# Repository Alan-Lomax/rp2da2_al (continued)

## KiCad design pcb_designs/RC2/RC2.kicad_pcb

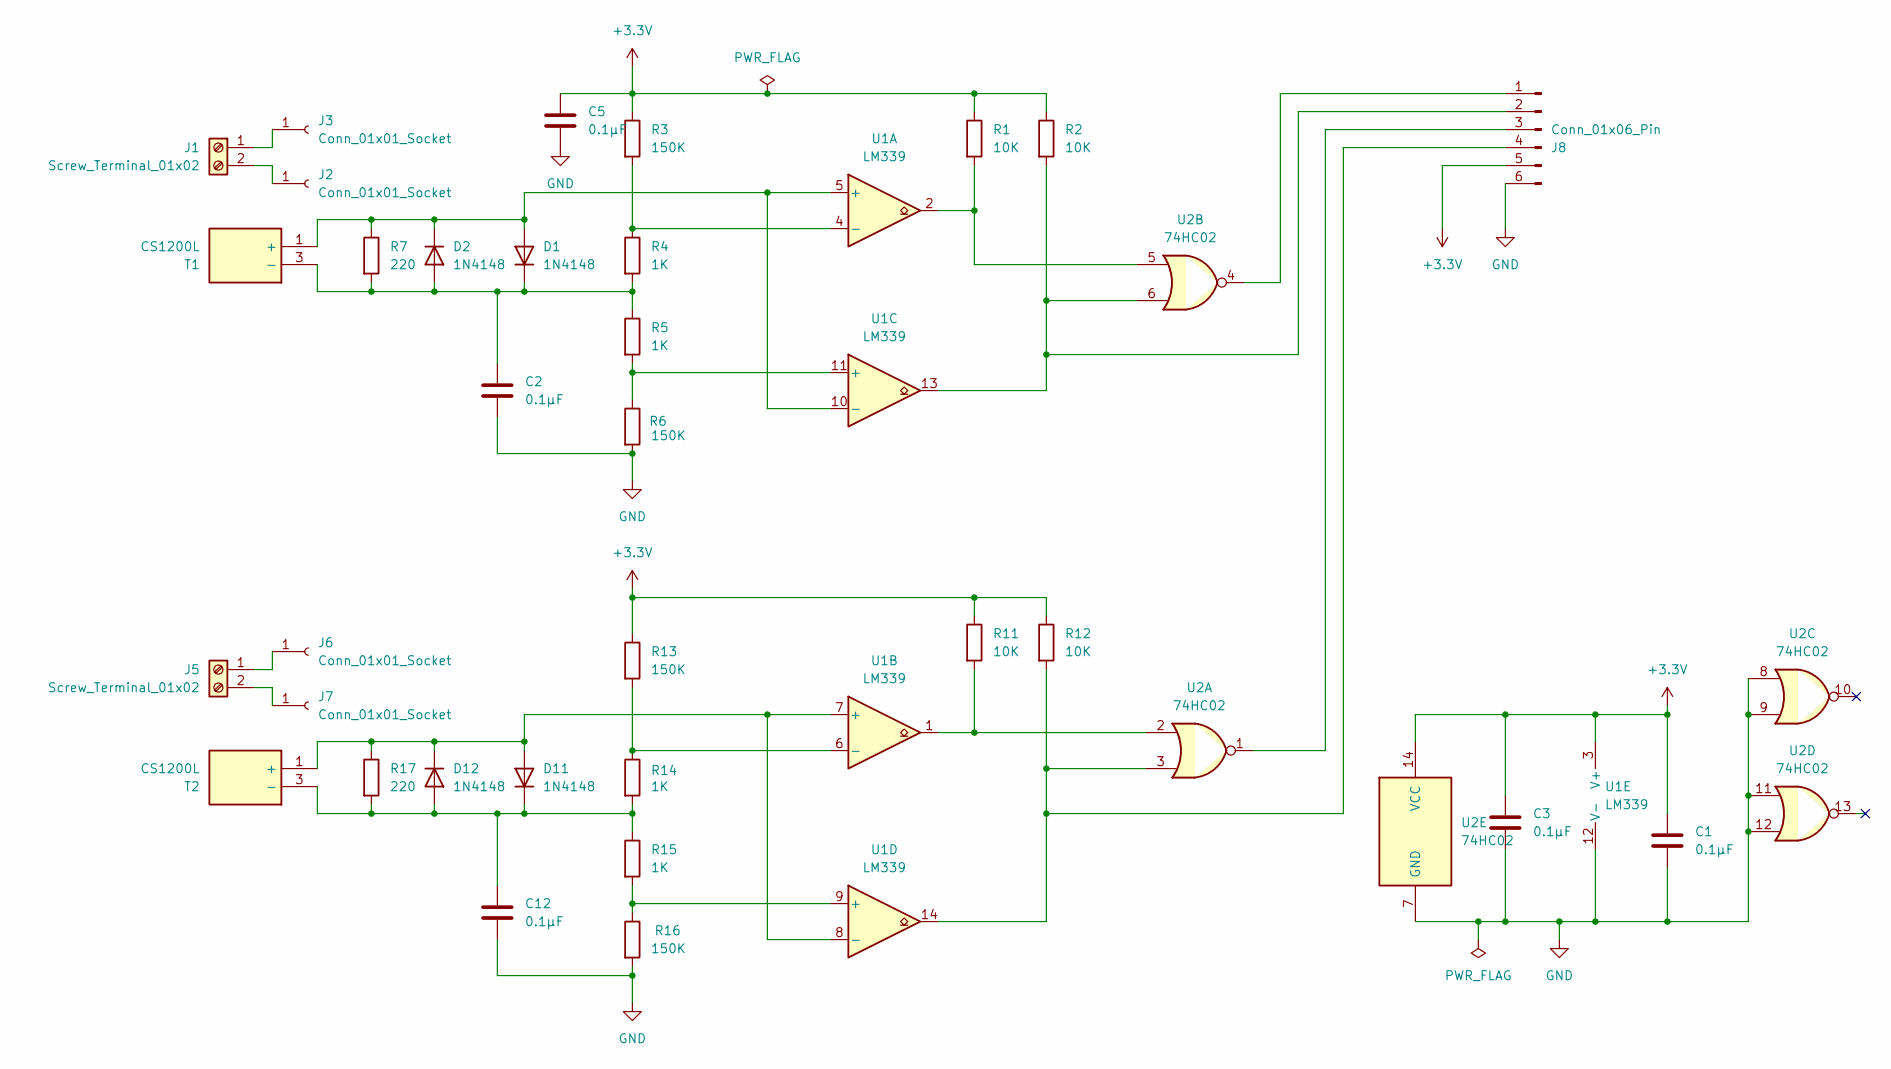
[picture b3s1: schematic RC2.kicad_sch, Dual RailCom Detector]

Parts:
C1, C2, C3, C5, C12: 0.1µF; C_Disc_D7.0mm_W2.5mm_P5.00mm
D1, D2, D11, D12: 1N4148; D_DO-35_SOD27_P7.62mm_Horizontal
J1, J5: Screw_Terminal_01x02; TerminalBlock_bornier-2_P5.08mm
J2, J3, J6, J7: Conn_01x01_Socket; SolderWire-0.5sqmm_1x01_D0.9mm_OD2.1mm
J8: Conn_01x06_Pin; Molex_KK-254_AE-6410-06A_1x06_P2.54mm_Vertical
R1, R2, R11, R12: 10K; R_Axial_DIN0207_L6.3mm_D2.5mm_P7.62mm_Horizontal
R3, R6, R13, R16: 150K; R_Axial_DIN0207_L6.3mm_D2.5mm_P7.62mm_Horizontal
R4, R5, R14, R15: 1K; R_Axial_DIN0207_L6.3mm_D2.5mm_P7.62mm_Horizontal
R7, R17: 220; R_Axial_DIN0207_L6.3mm_D2.5mm_P7.62mm_Horizontal
T1, T2: CS1200L; Manufacturer_Part_Number CS1200L; Mouser Part Number 994-CS1200L
U1: LM339; DIP-14_W7.62mm
U2: 74HC02; DIP-14_W7.62mm

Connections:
+3.3V: C1.1, C3.1, C5.1, J8.5, R1.1, R2.1, R3.1, R11.1, R12.1, R13.1, U1.3 (V+), U2.14 (VCC)
GND: C1.2, C2.2, C3.2, C5.2, C12.2, J8.6, R6.2, R16.2, U1.12 (V-), U2.7 (GND), U2.8, U2.9, U2.11, U2.12
unnamed: D1.2 (A), D2.1 (K), R7.1, T1.1 (+), U1.5 (+), U1.10 (-)
unnamed: C2.1, D1.1 (K), D2.2 (A), R4.2, R5.1, R7.2, T1.3 (-)
unnamed: D11.2 (A), D12.1 (K), R17.1, T2.1 (+), U1.7 (+), U1.8 (-)
unnamed: C12.1, D11.1 (K), D12.2 (A), R14.2, R15.1, R17.2, T2.3 (-)
unnamed: J1.1, J3.1
unnamed: J1.2, J2.1
unnamed: J5.1, J6.1
unnamed: J5.2, J7.1
unnamed: J8.1, U2.4
unnamed: J8.2, R2.2, U1.13, U2.6
unnamed: J8.3, U2.1
unnamed: J8.4, R12.2, U1.14, U2.3
unnamed: R1.2, U1.2, U2.5
unnamed: R11.2, U1.1, U2.2
unnamed: R3.2, R4.1, U1.4 (-)
unnamed: R13.2, R14.1, U1.6 (-)
unnamed: R5.2, R6.1, U1.11 (+)
unnamed: R15.2, R16.1, U1.9 (+)

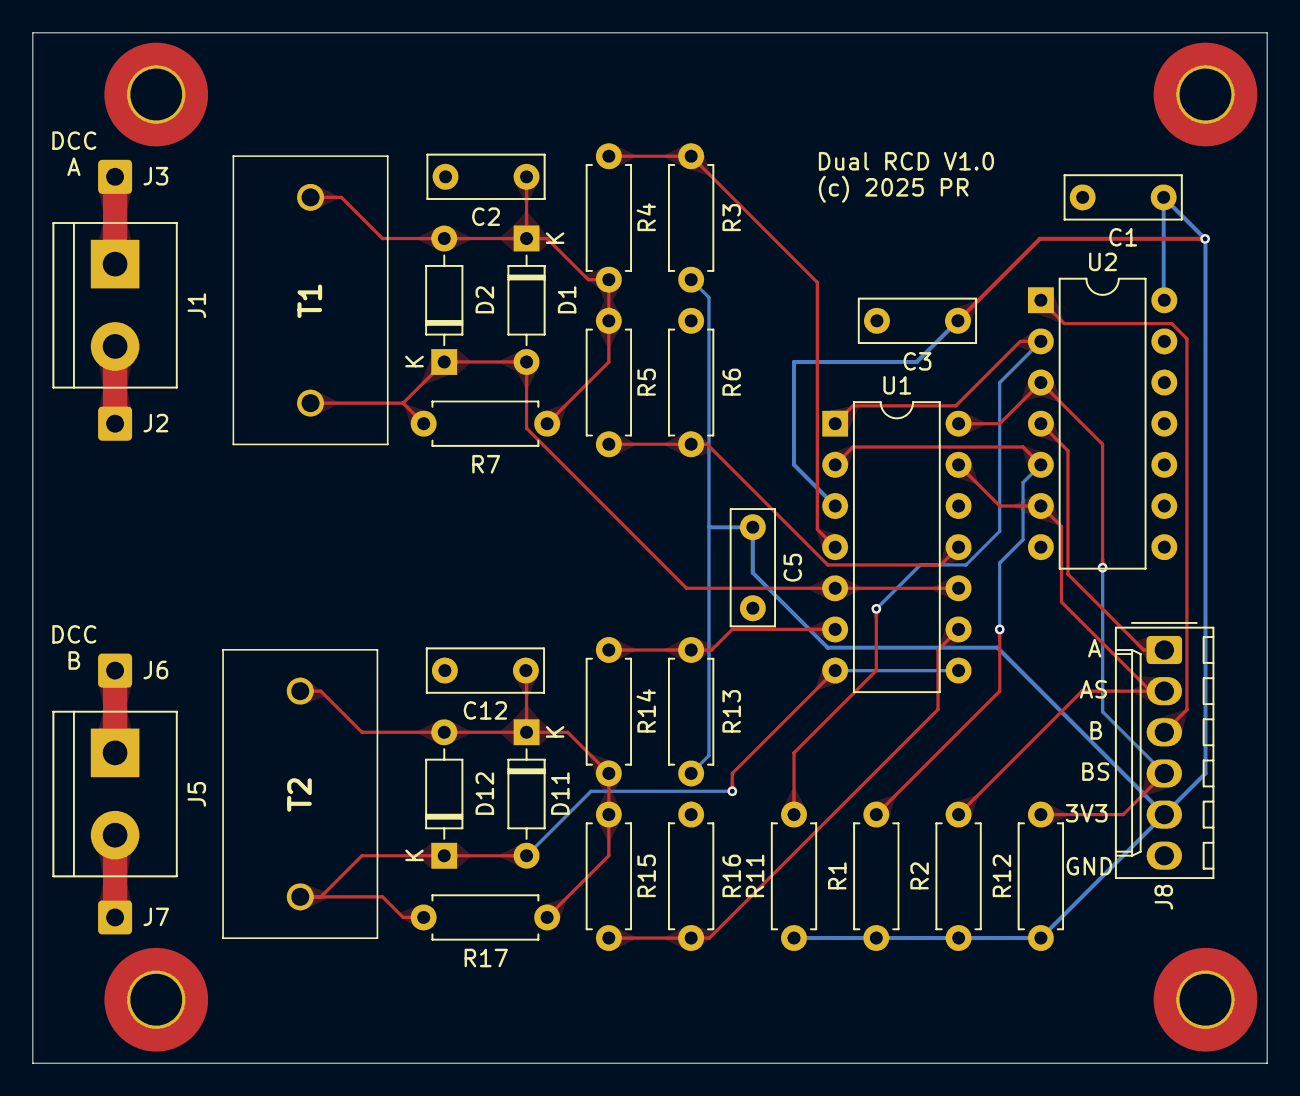
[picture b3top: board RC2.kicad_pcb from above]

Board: 2 copper layers, 76.2 x 63.6 mm, 34 parts (0 on the bottom side), 20 nets.

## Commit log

2025-04-23 Added diagnostics and other changes.
    This update provides additional diagnostic information on RailCom performance. There's also a bug fix related to parsing Channel 2 responses and other minor mostly cosmetic changes.
2025-04-29 PCB Design Added
    This update adds the Kicad PBC design to the repository.
    Software changes include improved start bit recognition and addition of the Programming on Main write CV function.
2025-05-26 Updated Schematic
    Up date to the dual detector schematic. N.B PCB layout to follow.
    Plus a few cosmetic code changes.
2025-06-03 New PCB Layout R2.1
    This new PCB Layout includes Raspberry Pi PICO footprint c/w Power Supply (12 VDC in to 5VDC out), A NeoPixel, an H Bridge Driver, an I2C OLED header, and many GPIO headers.
2025-06-03 GPIO Mappings etc.
    1. GPIO mappings for Pico changed to match PCB.
    2. GPIO allocations for DRV8874 _FAULT & Current Sense Added.
    3. README updated with installation instructions.
    4. Minor typos & bugs corrected.
2025-06-25 Orientation bit timing fix
    Fixes bug in reading orientation bit timing in PIO rx routine.
    git ignore Kicad lock files.
    Other cosmetic changes.
2025-06-25 kicad lock file removed
2025-07-16 Added PCB RC3
    Added Integrated Command Station PCB Design.
    Cosmetic changes to software.
2025-09-03 Tighten RailCom window timings etc
    Review and tighten RailCom window timings.
    Improved diagnostics and statistics.
    Refactoring to streamline timer callbacks.
    Cosmetic changes to formatting.
2025-09-11 RailCom Channel 1 improvements
    Elimination of potential race conditions on RailCom Channel 1.
    Plus the usual minor cosmetic stuff.
2025-10-03 asyncio introduction
    Refactor and modify MQTT interface to use asyncio.
2025-10-03 Als quality review. Very minor readability issues.
    Duplicated the GNDPWR symbol and used it to eliminated many crossed lines.
2025-10-08 Added RC3_PCB_R1b folder and contents
2025-10-09 Quad local detector
    Add example main.py for quad local detector.
    Minor bugs.
    Refactoring to improve RailCom decode performance.
2025-10-09 PCB Designs Split to new repo
    PCB Designs are now in rp2da2-pcb
2025-11-03 Update test_dccrc1.py
    Fix reference to undeclared pin
2026-03-25 Updates for board RC_LCL_4 Rev 0.B
    Updates to allow Revision 0.B of the RC_LCL-4 board.
    Other minor and cosmetic changes.
2026-05-07 Refactor local detectors, ADC, PIO and docs
    Large refactor and docs updates to improve local detector reliability and usability. Key changes: add dcc_pin support to local RCom detectors and pass DCC sense pin from examples; rewrite ADC reading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
2026-05-30 Publish RailCom ch2 dynamic info; UI/README fixes
    Add end-to-end support for RailCom Channel-2 dynamic information and several UI/docs fixes.
    Key changes:
    - RComCmdRsp (rp2dcc/dcc_rc_ch2.py): make detector a singleton, store dynamic values, enqueue changed addresses with a bounded deque, and signal queue-full via Device.CH2_Q_FULL. Provide get_instance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
    - MQTT publishing (lib/mqtt_cmd.py): start a background _pub_check task in Cab to poll RComCmdRsp.get_dyn_chng() and publish JSON payloads to rcom/gbl/{addr}/id7. Add _DYN_INFO_ENCODE mapping and rep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
    - Screen/UI (lib/screen.py): handle and display unencoded ID7 e
2026-06-01 Refactor local-board tests; add Wi-Fi test
    Fixes and refactors board commissioning tests and adds a new Wi‑Fi test script.
    Key changes:
    - test/test_cs_bd.py: Fix I2C pin checks to use Pin.value(), correct neopixel color assignments and logic in scan_i2c.
    - test/test_lcl_bd.py: Major refactor and feature additions:
    - Add constants for colors, Timer, unique_id, and micropython imports.
    - Rename and separate RX/orientation pin lists; update i2c pin mapping.
2026-06-01 Create test_wifi.py
    Added a standalone test file for connecting to wifi
2026-06-01 Update test_wifi.py
    Restore test_wifi.py - recovered from commit db9fd6c
2026-06-06 Add commissioning test scripts for WiFi and MQTT
